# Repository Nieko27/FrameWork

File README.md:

## Note
A forewarning, I am very new to electronics design in general. I apologize in advance for any really baffling design decisions. I hope to learn from these projects and will keep them updated as I learn more. Thank you for your patience.

> ⚠️This is an unofficial 3rd-party project with no association to Valve.

# What is Frame Workshop?
Frame Workshop is intended to be an open-source bundle of different hardware peripherals built around (but not always exclusive to) the Steam Frame. The idea is to leverage the Steam Frames' modularity and general openness to create a collection of open-source hardware projects that the community can provide feedback on, expand upon, or even take and turn into something entirely new, creating a feedback loop that adds to an ever-expanding ecosystem for the Steam Frame. All source files, from schematics to STLs, will be included, allowing every aspect of each project to be modified and produced to anyone’s preferences. 

## Hardware
Below is a list of all currently in development hardware projects, including a brief overview and notes on changes made to the most recent revision.

### Frame Facetracker
The Frame face tracker is pretty self-explanatory: it is a module that uses a camera for face tracking in social experiences like VRChat. There are 2 versions planned: one built with the steam frame in mind, using its expansion ports, and another that plugs into the back USB port of the frame and uses an ESP32 to run the camera.

Link to the facetracker files:
https://github.com/Nieko27/FrameWork/tree/main/KICAD%20Projects/Primis_FaceTracker

### Versipellis (General Purpose Dongle)
Versipellis is a dongle utilising an nRF52833 intended as a general-purpose dongle for communicating with any Frame-based hardware, whether it be controllers or trackers. It will be programmable by the end user for whatever they intend to use it for. There will be two versions: one utilising no parts smaller than a 0603 package, making it easy to hand-assemble, and another using much smaller parts that, while smaller, will require assembly by a service like JLCPCB.

Link to Versipellis' files:
https://github.com/Nieko27/FrameWork/tree/main/KICAD%20Projects/Primis_Versipellis

### Locus (Tracker)
Locus is intended to be a tracker like Vive or Tundra, but without reliance on lighthouse base stations. Since the Steam Frame isn’t limited to base station vision, trackers being used with it shouldn’t be either. Similar to Versipellis, Locus will also use an nRF52833 along with an LSM6DSV16X IMU and a QMC6309 magnetometer. The idea is that it will track similarly to a slime tracker, but also use the Steam Frame’s optical tracking to address the drift problem of EMF trackers. 

Link to Locus' files:
https://github.com/Nieko27/FrameWork/tree/main/KICAD%20Projects/Primis_Locus

## Project Goals

* Keep costs to the users as low as possible. You've probably already spent close to $1000 on the headset itself, so it would be nice not to have to spend another $1000 customizing it to your liking. How this would be achieved is by everything being open and nothing being sold, for example I’m working on a face tracker that takes advantage of the PCIe port on the Frame, the idea is when its done instead of me having to handle production, shipping and all the joys of selling a project I give the source files out with a tutorial on how to order it yourself from a company like JLCPCB. Now, obviously, this still won't be free to the end user, but it will be much cheaper than if I were to sell it. For example, I have made the first prototype of the face-tracker, and in small quantities (5 to be exact), it cost me $25 per board. Compare that to something like the old Vive face trackers, which I think were closer to $100, and you save a nice bit of money. 

* Give the end user total control over the hardware. Don't like how I've done something? Fire up Blender or KiCad and change it yourself to fit whatever need you have in mind. I know not everyone will be able to do this, as it requires familiarity with the software, but it gives people the ability to do so. Obviously, with this in mind, I want to make the experience for everyone as smooth as possible out of the box, so I will be listening to feedback as much as possible to achieve that. 

* Create a feedback loop. I have all this under a CERN-OHL-S-2.0 license, which (as far as I understand) means you can do anything you want with anything in the repo, including selling it for profit, but you must open-source anything you do under the same license. This way it keeps everything open to the community, and every addition helps grow the ecosystem around the Steam Frame. 

## Ideas
A few ideas for possible mods for the Frame have already been thrown around. If you have an idea for a mod, whether it's a full module or as simple as a 3D-printable counterweight, feel free to open a pull request under the enhancement tag. You may also feel free to email me at nieko972@gmail.com.

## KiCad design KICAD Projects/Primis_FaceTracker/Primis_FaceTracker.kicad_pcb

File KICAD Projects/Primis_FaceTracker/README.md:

### WARNING
This has yet to be produced by me yet, I have not yet added the gerber files to this repo yet as I have no idea if it will work yet, order them at your own risk.
# Face Tracker (Headset-Agnostic Version)
Headset-agnostic face tracker. Can be used with Frame by using the USB-C port on the battery.

### Schematics

### PCB

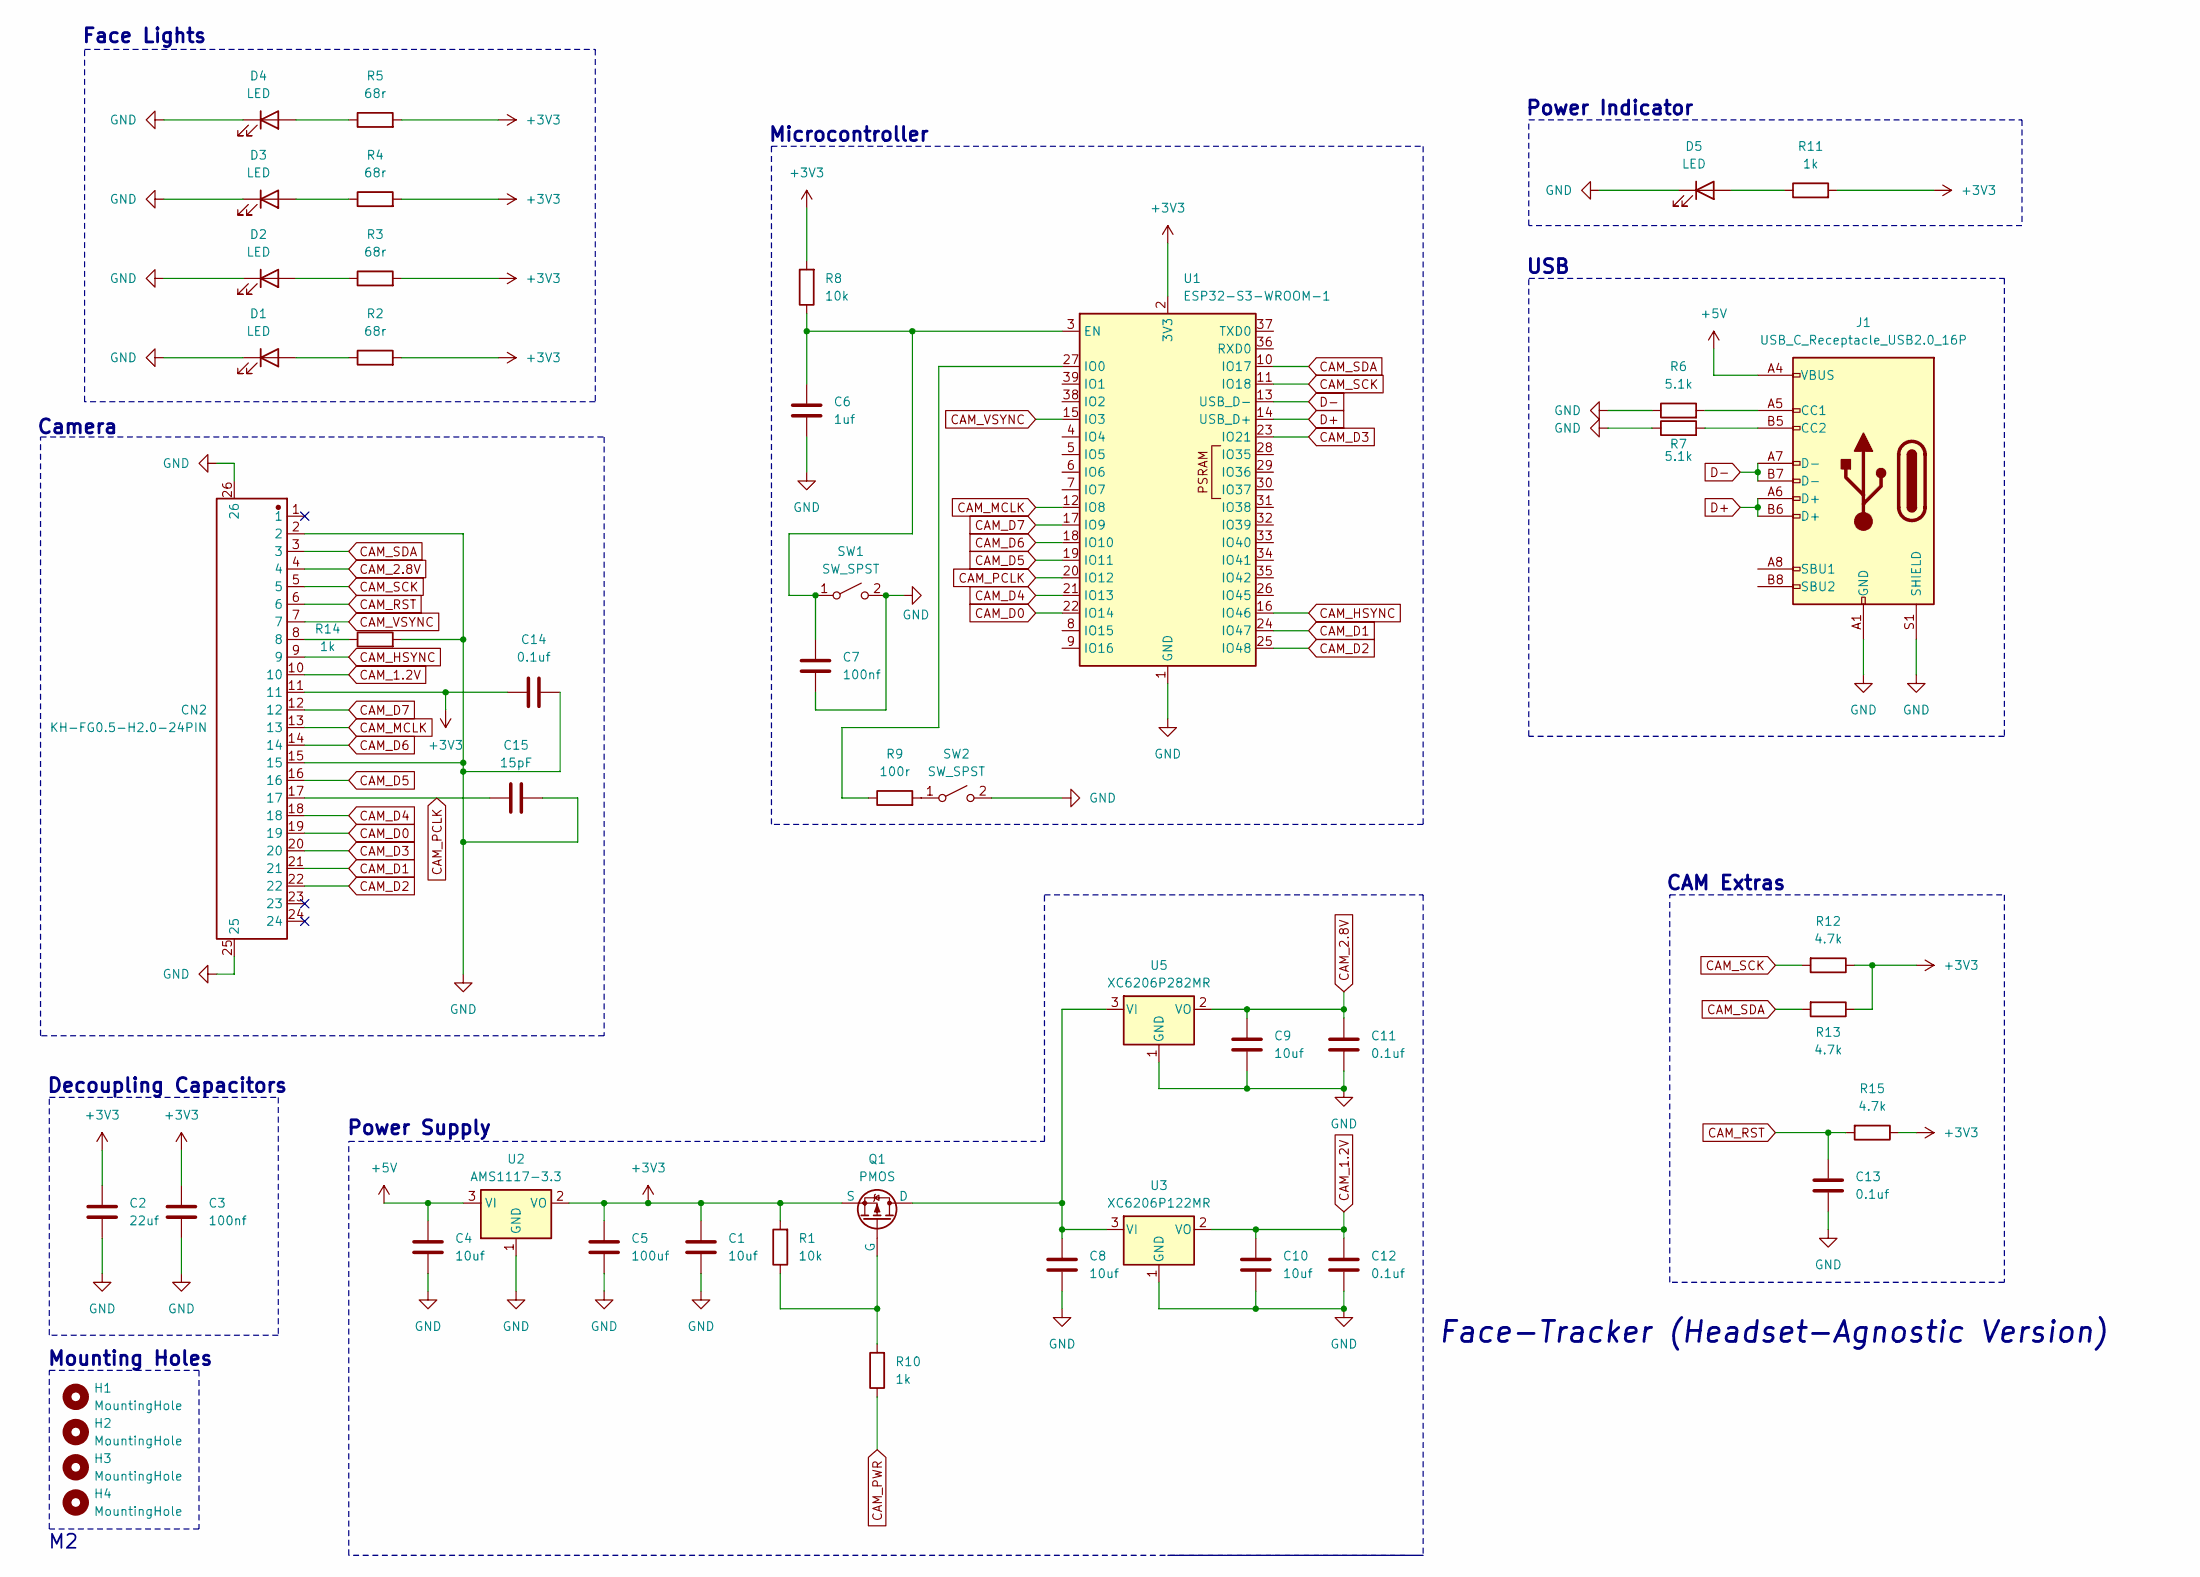
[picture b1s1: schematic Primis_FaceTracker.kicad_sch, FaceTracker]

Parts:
C1, C4, C8, C9, C10: 10uf; C_0805_2012Metric
C2: 22uf; C_0805_2012Metric
C3, C7: 100nf; C_0603_1608Metric
C5: 100uf; C_1206_3216Metric
C6: 1uf; C_0603_1608Metric
C11, C12, C13, C14: 0.1uf; C_0603_1608Metric
C15: 15pF; C_0603_1608Metric
CN2: KH-FG0.5-H2.0-24PIN; FPC-SMD_KH-FG0.5-H2.0-24PIN
D1, D2, D3, D4, D5: LED; LED_0805_2012Metric
H1, H2, H3, H4: MountingHole; MountingHole_2.2mm_M2
J1: USB_C_Receptacle_USB2.0_16P; USB_C_Receptacle_HRO_TYPE-C-31-M-12
Q1: PMOS; SOT-23
R1, R8: 10k; R_0805_2012Metric
R2, R3, R4, R5: 68r; R_0603_1608Metric
R6, R7: 5.1k; R_0805_2012Metric
R9: 100r; R_0603_1608Metric
R10, R11, R14: 1k; R_0805_2012Metric
R12, R13, R15: 4.7k; R_0805_2012Metric
SW1, SW2: SW_SPST; SW_SPST_TS-1088-xR020
U1: ESP32-S3-WROOM-1
U2: AMS1117-3.3; SOT-223-3_TabPin2
U3: XC6206P122MR; SOT-23-3
U5: XC6206P282MR; SOT-23-3

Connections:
+3V3: C1.1, C2.1, C3.1, C5.1, C14.1, CN2.11, Q1.3 (S), R1.2, R2.2, R3.2, R4.2, R5.2, R8.2, R11.2, R12.1, R13.1, R15.1, U1.2 (3V3), U2.2 (VO)
+5V: C4.1, J1.A4 (VBUS), J1.A9 (VBUS), J1.B4 (VBUS), J1.B9 (VBUS), U2.3 (VI)
CAM_1.2V: C10.1, C12.1, CN2.10, U3.2 (VO)
CAM_2.8V: C9.1, C11.1, CN2.4, U5.2 (VO)
CAM_D0: CN2.19, U1.22 (IO14)
CAM_D1: CN2.21, U1.24 (IO47)
CAM_D2: CN2.22, U1.25 (IO48)
CAM_D3: CN2.20, U1.23 (IO21)
CAM_D4: CN2.18, U1.21 (IO13)
CAM_D5: CN2.16, U1.19 (IO11)
CAM_D6: CN2.14, U1.18 (IO10)
CAM_D7: CN2.12, U1.17 (IO9)
CAM_HSYNC: CN2.9, U1.16 (IO46)
CAM_MCLK: CN2.13, U1.12 (IO8)
CAM_PCLK: C15.1, CN2.17, U1.20 (IO12)
CAM_PWR: R10.1
CAM_RST: C13.1, CN2.6, R15.2
CAM_SCK: CN2.5, R12.2, U1.11 (IO18)
CAM_SDA: CN2.3, R13.2, U1.10 (IO17)
CAM_VSYNC: CN2.7, U1.15 (IO3)
D+: J1.A6 (D+), J1.B6 (D+), U1.14 (USB_D+)
D-: J1.A7 (D-), J1.B7 (D-), U1.13 (USB_D-)
GND: C1.2, C2.2, C3.2, C4.2, C5.2, C6.2, C7.1, C8.2, C9.2, C10.2, C11.2, C12.2, C13.2, C14.2, C15.2, CN2.2, CN2.15, CN2.25, CN2.26, D1.1 (K), D2.1 (K), D3.1 (K), D4.1 (K), D5.1 (K), J1.A1 (GND), J1.A12 (GND), J1.B1 (GND), J1.B12 (GND), J1.S1 (SHIELD), R6.1, R7.1, R14.2, SW1.2 (B), SW2.2 (B), U1.1 (GND), U1.40 (GND), U1.41 (GND), U2.1 (GND), U3.1 (GND), U5.1 (GND)
unnamed: CN2.8, R14.1
unnamed: D1.2 (A), R2.1
unnamed: D2.2 (A), R3.1
unnamed: D3.2 (A), R4.1
unnamed: D4.2 (A), R5.1
unnamed: D5.2 (A), R11.1
unnamed: J1.A5 (CC1), R6.2
unnamed: J1.B5 (CC2), R7.2
unnamed: C8.1, Q1.1 (D), U3.3 (VI), U5.3 (VI)
unnamed: Q1.2 (G), R1.1, R10.2
unnamed: C6.1, C7.2, R8.1, SW1.1 (A), U1.3 (EN)
unnamed: R9.2, SW2.1 (A)
unnamed: R9.1, U1.27 (IO0)

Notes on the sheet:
Decoupling Capacitors
Face Lights
Mounting Holes
Microcontroller
Power Indicator
Face-Tracker (Headset-Agnostic Version)
USB
Camera
CAM Extras
Power Supply

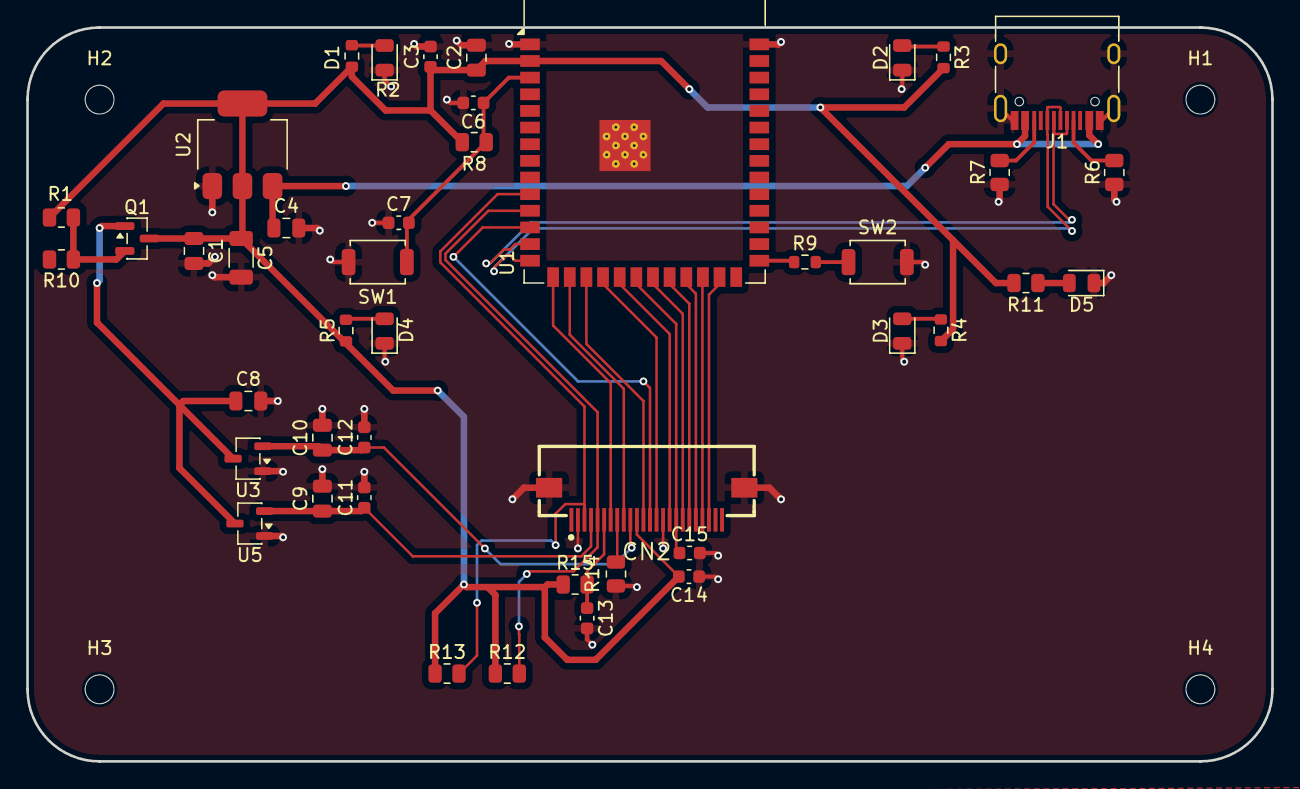
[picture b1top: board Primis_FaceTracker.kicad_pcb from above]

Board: 2 copper layers, 95.0 x 56.0 mm, 48 parts (0 on the bottom side), 35 nets.

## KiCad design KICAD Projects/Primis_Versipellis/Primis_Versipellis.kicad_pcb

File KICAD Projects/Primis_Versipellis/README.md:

### WARNING
This has yet to be produced by me yet, I have not yet added the gerber files to this repo yet as I have no idea if it will work yet, order them at your own risk.
# Versipellis
The general purpose dongle for the Steam Frame.

### Schematics

### PCB

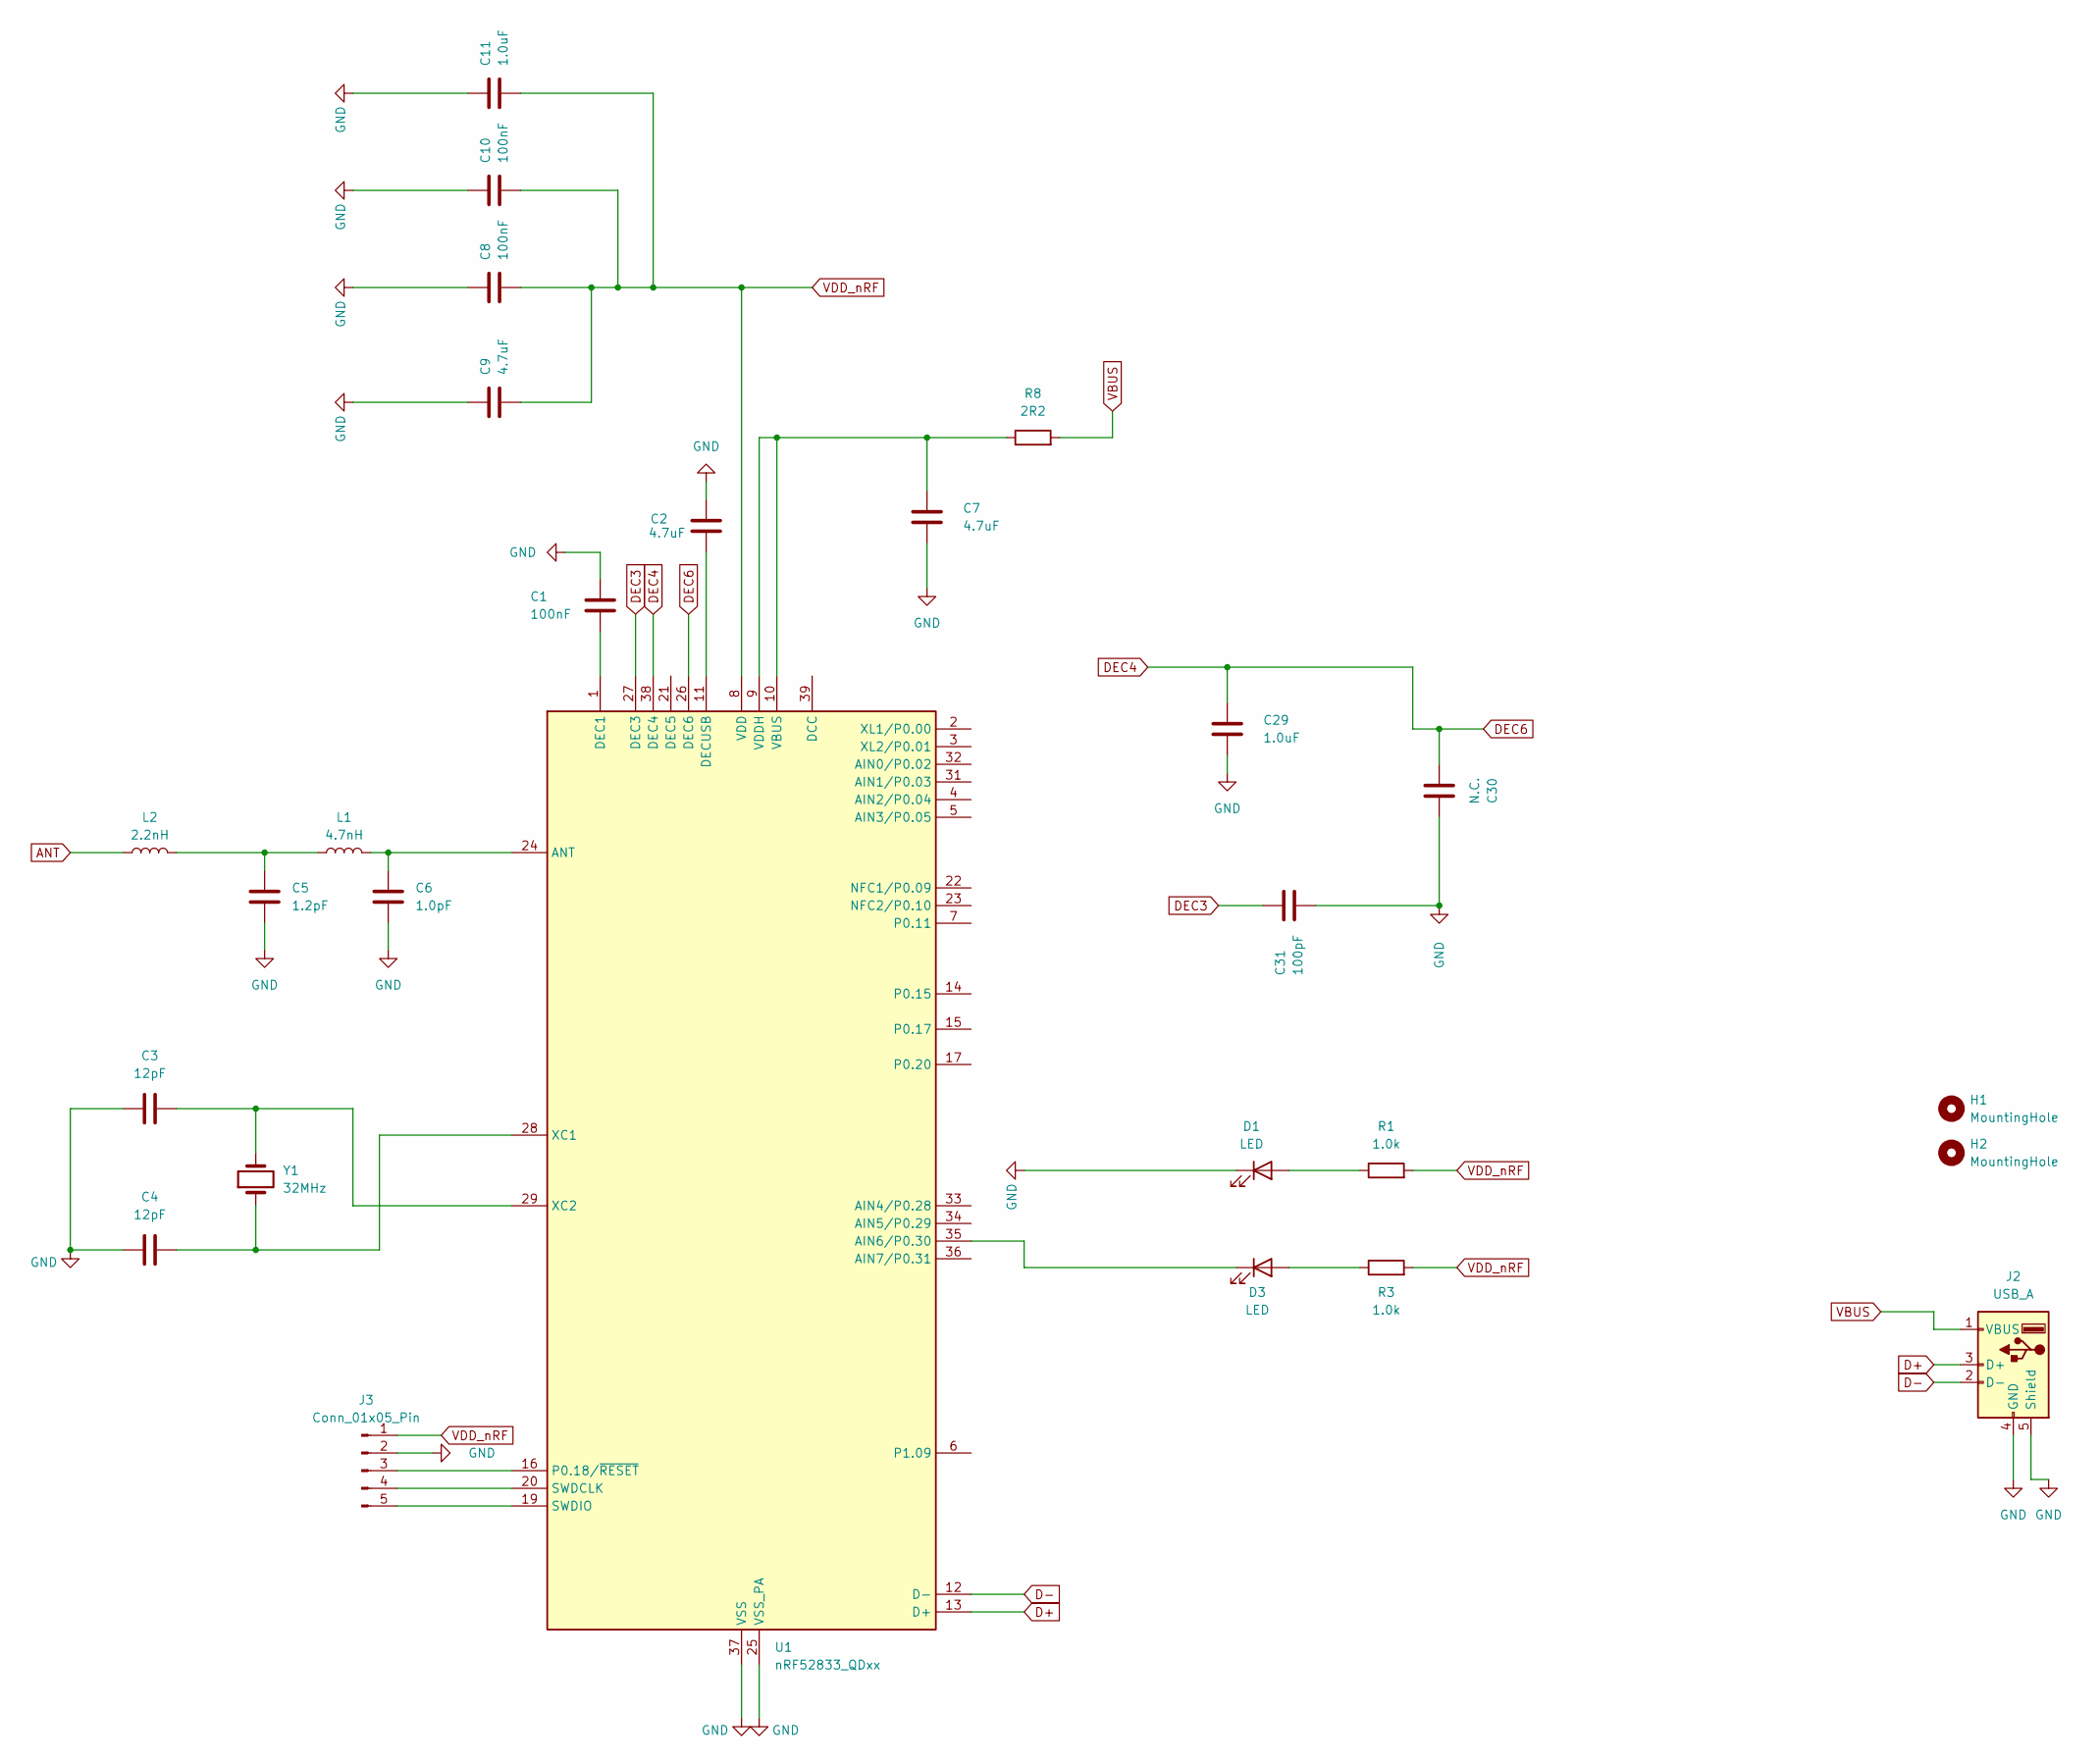
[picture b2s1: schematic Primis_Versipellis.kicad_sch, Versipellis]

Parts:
C1, C8, C10: 100nF; C_0603_1608Metric
C2, C7, C9: 4.7uF; C_0603_1608Metric
C3, C4: 12pF; C_0603_1608Metric
C5: 1.2pF; C_0603_1608Metric
C6: 1.0pF; C_0603_1608Metric
C11, C29: 1.0uF; C_0603_1608Metric
C30: N.C.; C_0603_1608Metric
C31: 100pF; C_0603_1608Metric
D1, D3: LED; LED_0603_1608Metric
H1, H2: MountingHole; MountingHole_2.2mm_M2
J2: USB_A; USB_A_CNCTech_1001-011-01101_Horizontal
J3: Conn_01x05_Pin; PinHeader_1x05_P1.00mm_Vertical
L1: 4.7nH; L_0603_1608Metric
L2: 2.2nH; L_0603_1608Metric
R1, R3: 1.0k; R_0603_1608Metric
R8: 2R2; R_0805_2012Metric
U1: nRF52833_QDxx; QFN-40-1EP_5x5mm_P0.4mm_EP3.6x3.6mm
Y1: 32MHz; Crystal_SMD_5032-2Pin_5.0x3.2mm

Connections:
ANT: L2.1
D+: J2.3 (D+), U1.13 (D+)
D-: J2.2 (D-), U1.12 (D-)
DEC3: C31.1, U1.27 (DEC3)
DEC4: C29.1, C30.2, U1.26 (DEC6), U1.38 (DEC4)
GND: C1.1, C2.2, C3.1, C4.1, C5.1, C6.1, C7.2, C8.1, C9.2, C10.1, C11.2, C29.2, C30.1, C31.2, D1.1 (K), J2.4 (GND), J2.5 (Shield), J3.2, U1.25 (VSS_PA), U1.37 (VSS), U1.41 (VSS)
unnamed: C5.2, L1.1, L2.2
unnamed: D1.2 (A), R1.1
unnamed: D3.2 (A), R3.1
unnamed: D3.1 (K), U1.35 (AIN6/P0.30)
unnamed: J3.3, U1.16 (P0.18/~RESET)
unnamed: J3.4, U1.20 (SWDCLK)
unnamed: J3.5, U1.19 (SWDIO)
unnamed: C6.2, L1.2, U1.24 (ANT)
unnamed: C1.2, U1.1 (DEC1)
unnamed: C2.1, U1.11 (DECUSB)
unnamed: C7.1, R8.1, U1.9 (VDDH), U1.10 (VBUS)
unnamed: C4.2, U1.28 (XC1), Y1.1
unnamed: C3.2, U1.29 (XC2), Y1.2
VBUS: J2.1 (VBUS), R8.2
VDD_nRF: C8.2, C9.1, C10.2, C11.1, J3.1, R1.2, R3.2, U1.8 (VDD), U1.18 (VDD), U1.30 (VDD), U1.40 (VDD)

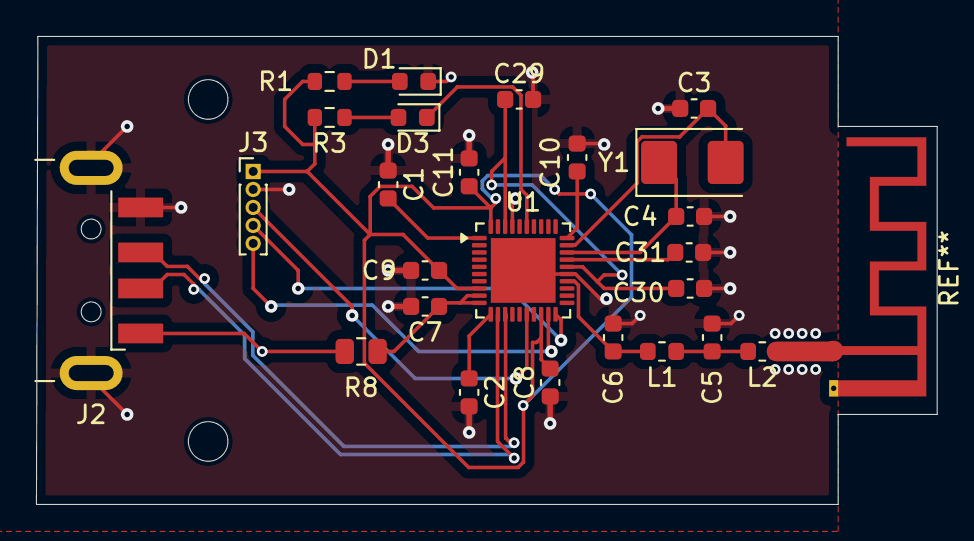
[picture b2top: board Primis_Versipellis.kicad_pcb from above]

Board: 2 copper layers, 50.0 x 26.0 mm, 27 parts (0 on the bottom side), 20 nets.

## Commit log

2026-01-17 Update LICENSE
2026-01-22 First Commit
    Upload of mostly everything so far.
    -V1 untested Versipellis
    -Dev files of Locus
    -Shared files used from componentsearchengine.com/
2026-01-22 VIMGS
2026-01-24 Versipellis Update 1
    -Fixed VDD
2026-01-26 House Keeping
    -Added stub files for facetracker EV2
    -Updated Logo and main readme
2026-02-07 Face Tracker WIP Commit
    First commit for the face tracker
    -Added face tracker schematics
    -Added stub for face tracker PCBs
2026-02-10 Face Tracker PCB
    -Some work on the PCB, not quite done but I'm making some changes so uploading as a backup.
2026-02-11 Face Tracker V1
    -Roughly finished face tracker PCB
    -Organised face tracker schematics
    -Added face tracker images
    -Added USB-C and FPC port models
    -Updated README
